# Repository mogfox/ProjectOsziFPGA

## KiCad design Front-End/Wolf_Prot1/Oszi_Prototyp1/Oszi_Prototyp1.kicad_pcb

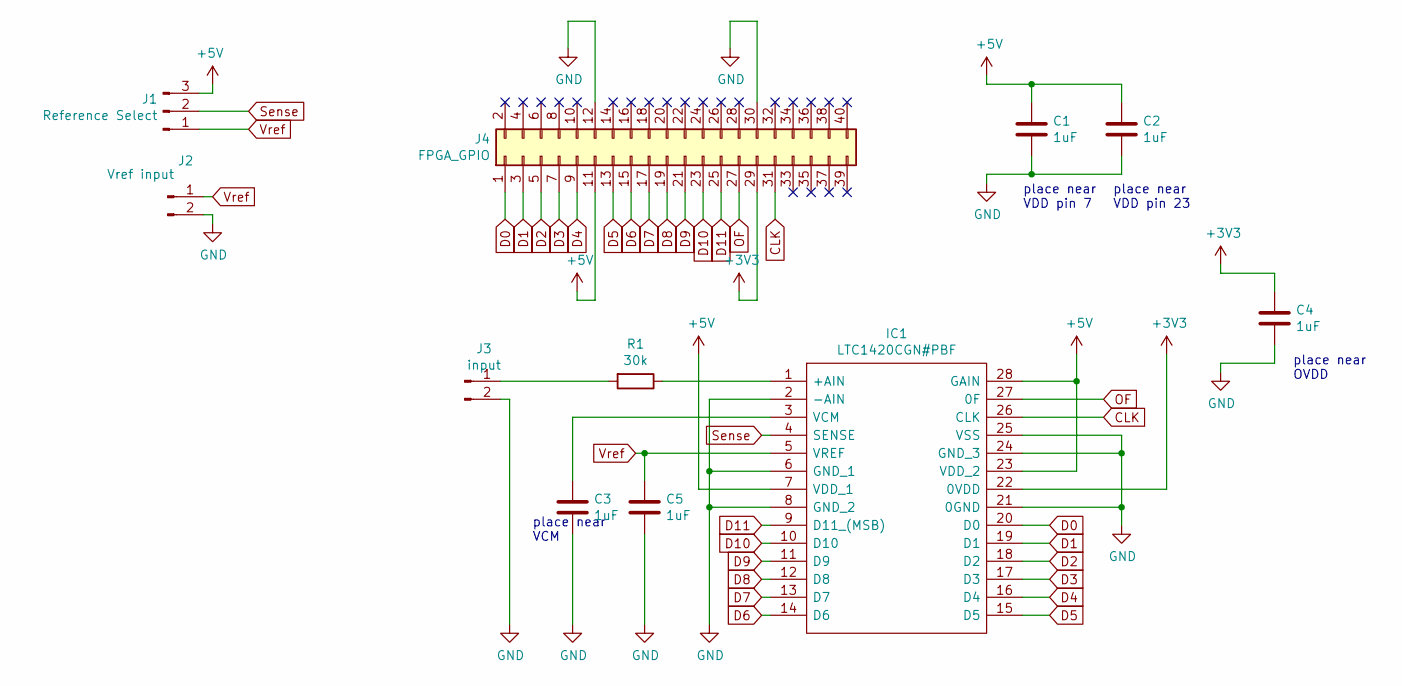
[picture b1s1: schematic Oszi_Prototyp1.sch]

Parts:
C1, C2, C3, C4, C5: 1uF; C_1206_3216Metric_Pad1.42x1.75mm_HandSolder
IC1: LTC1420CGN#PBF; SOP64P601X175-28N; Manufacturer_Part_Number LTC1420CGN#PBF; Mouser Part Number 584-LTC1420CGN#PBF
J1: Reference Select; PinHeader_1x03_P2.54mm_Vertical
J2: Vref input; PinHeader_1x02_P2.54mm_Vertical
J3: input; PinHeader_1x02_P2.54mm_Horizontal
J4: FPGA_GPIO; PinSocket_2x20_P2.54mm_Vertical
R1: 30k; R_0805_2012Metric_Pad1.15x1.40mm_HandSolder

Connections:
+3V3: C4.1, IC1.22 (0VDD), J4.29
+5V: C1.1, C2.1, IC1.7 (VDD_1), IC1.23 (VDD_2), IC1.28 (GAIN), J1.3, J4.11
CLK: IC1.26 (CLK), J4.31
D0: IC1.20 (D0), J4.1
D1: IC1.19 (D1), J4.3
D2: IC1.18 (D2), J4.5
D3: IC1.17 (D3), J4.7
D4: IC1.16 (D4), J4.9
D5: IC1.15 (D5), J4.13
D6: IC1.14 (D6), J4.15
D7: IC1.13 (D7), J4.17
D8: IC1.12 (D8), J4.19
D9: IC1.11 (D9), J4.21
D10: IC1.10 (D10), J4.23
D11: IC1.9 (D11_(MSB)), J4.25
GND: C1.2, C2.2, C3.2, C4.2, C5.2, IC1.2 (-AIN), IC1.6 (GND_1), IC1.8 (GND_2), IC1.21 (0GND), IC1.24 (GND_3), IC1.25 (VSS), J2.2, J3.2, J4.12, J4.30; also elsewhere on the board
unnamed: C3.1, IC1.3 (VCM)
unnamed: IC1.1 (+AIN), R1.1
unnamed: J3.1, R1.2
OF: IC1.27 (0F), J4.27
Sense: IC1.4 (SENSE), J1.2
Vref: C5.1, IC1.5 (VREF), J1.1, J2.1

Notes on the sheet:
place near VDD pin 7
place near OVDD
place near VDD pin 23
place near VCM

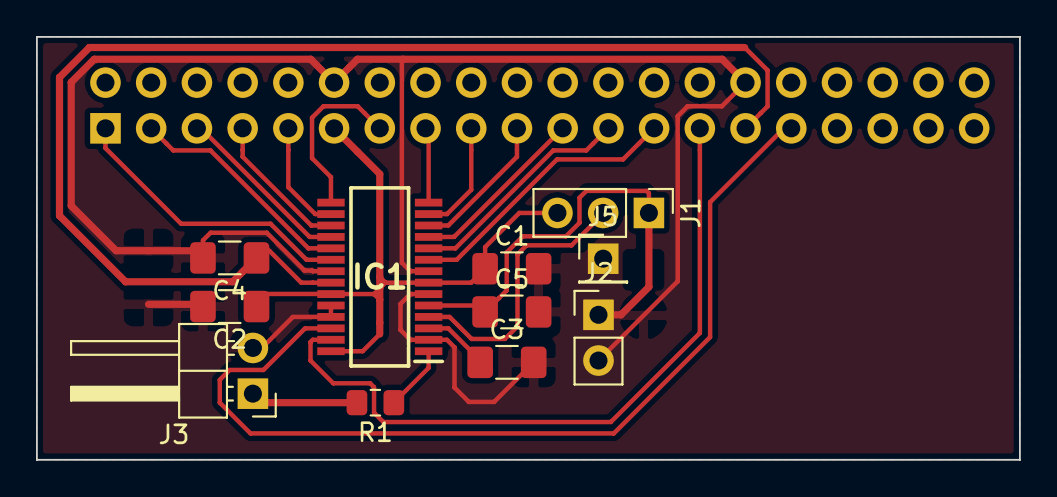
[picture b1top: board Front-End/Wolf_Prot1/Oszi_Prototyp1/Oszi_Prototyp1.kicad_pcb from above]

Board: 2 copper layers, 54.6 x 23.5 mm, 12 parts (1 on the bottom side), 22 nets.

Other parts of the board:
J5: Conn_01x01_Male; PinHeader_1x01_P2.54mm_Vertical

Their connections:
GND: J5.1; also elsewhere on the board

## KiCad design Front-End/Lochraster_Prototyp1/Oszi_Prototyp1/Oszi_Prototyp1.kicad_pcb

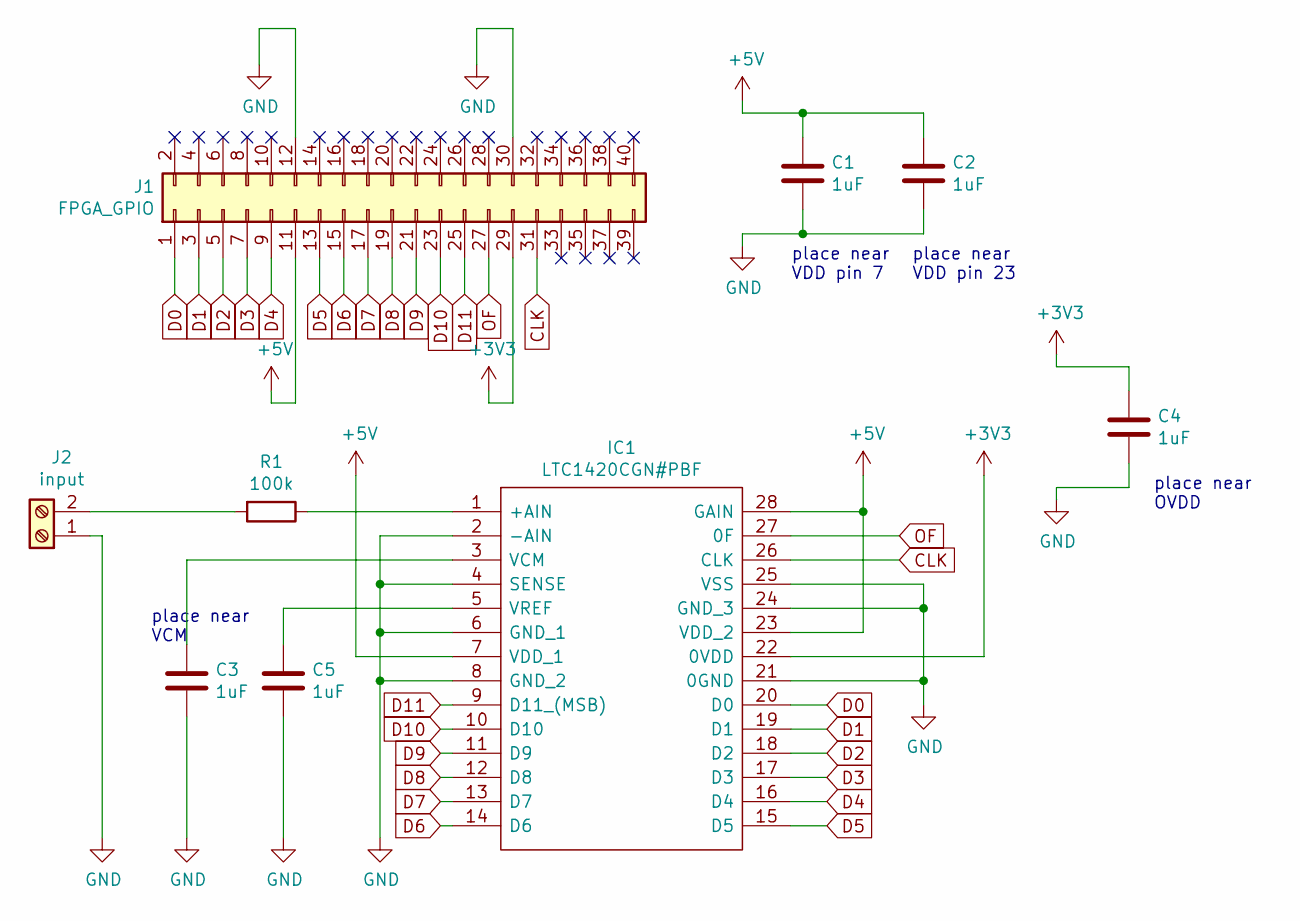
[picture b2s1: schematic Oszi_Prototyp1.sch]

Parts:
C1, C2, C3, C4, C5: 1uF; C_1206_3216Metric_Pad1.42x1.75mm_HandSolder
IC1: LTC1420CGN#PBF; SOP64P601X175-28N; Manufacturer_Part_Number LTC1420CGN#PBF; Mouser Part Number 584-LTC1420CGN#PBF
J1: FPGA_GPIO; PinSocket_2x20_P2.54mm_Vertical
J2: input; PinSocket_1x02_P2.54mm_Horizontal
R1: 100k; R_0805_2012Metric_Pad1.15x1.40mm_HandSolder

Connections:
+3V3: C4.1, IC1.22 (0VDD), J1.29
+5V: C1.1, C2.1, IC1.7 (VDD_1), IC1.23 (VDD_2), IC1.28 (GAIN), J1.11
CLK: IC1.26 (CLK), J1.31
D0: IC1.20 (D0), J1.1
D1: IC1.19 (D1), J1.3
D2: IC1.18 (D2), J1.5
D3: IC1.17 (D3), J1.7
D4: IC1.16 (D4), J1.9
D5: IC1.15 (D5), J1.13
D6: IC1.14 (D6), J1.15
D7: IC1.13 (D7), J1.17
D8: IC1.12 (D8), J1.19
D9: IC1.11 (D9), J1.21
D10: IC1.10 (D10), J1.23
D11: IC1.9 (D11_(MSB)), J1.25
GND: C1.2, C2.2, C3.2, C4.2, C5.2, IC1.2 (-AIN), IC1.4 (SENSE), IC1.6 (GND_1), IC1.8 (GND_2), IC1.21 (0GND), IC1.24 (GND_3), IC1.25 (VSS), J1.12, J1.30, J2.1
unnamed: C3.1, IC1.3 (VCM)
unnamed: C5.1, IC1.5 (VREF)
unnamed: IC1.1 (+AIN), R1.1
unnamed: J2.2, R1.2
OF: IC1.27 (0F), J1.27

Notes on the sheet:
place near VDD pin 7
place near OVDD
place near VDD pin 23
place near VCM

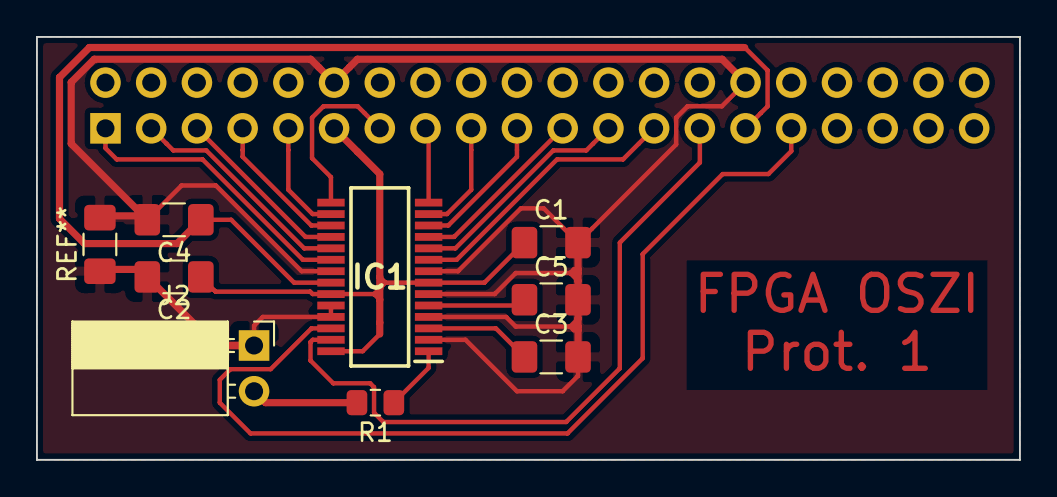
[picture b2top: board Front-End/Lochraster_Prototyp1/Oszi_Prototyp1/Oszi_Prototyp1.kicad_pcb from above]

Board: 2 copper layers, 54.6 x 23.5 mm, 9 parts (1 on the bottom side), 21 nets.

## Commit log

2021-02-11 Basic Project
2021-02-11 start
2021-03-17 17.03
2021-03-18 18.3.21
2021-03-18 18.03.2021
2021-03-18 18.03.202111:33:03,20
2021-03-18 18.03.202113:40:06,99
2021-03-18 18.03.202120:28:35,44
2021-03-18 18.03.202123:41:19,54
2021-03-22 22.03.202113:54:55,26
2021-03-25 25.03.202112:23:24,69
2021-04-08 08.04.202114:43:08,12
2021-04-15 15.04.202115:58:33,16
2021-04-15 15.04.202121:24:56,70
2021-04-22 22.04.202114:56:16,02
2021-04-29 29.04.202123:12:11,19
